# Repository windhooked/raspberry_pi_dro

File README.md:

# raspberry_pi_dro
Raspberry PI DRO for the Lathe, with Frequency drive control and soft stops

If you ever thought a manual lathe could be more intelligent, and a CNC lathe takes too long to program for one of jobs, this project might be for you. Thread cutting, the cut cycle is slow, the backout cycle is just as painfully slow. It wwoul dbe nice to have a seperate speed for cut and backout cycles.

Features:

1) Simple button controls for forward / Reverse and Stop
2) Set speed on forward and reverse cycles.
3) Soft stops
4) automatic tapping function with depth and reverse out
5) Direct Glass scale interface

Controls:

[ Forward ]        [ Clear ]
[ Reverse ] [Stop] [ Enter ] [ Rotary Enc ]

Functions:
  Fwd <Ent>       " Run forward
  Fwd <Rot> < Ent> " forward with speed adjust
  Rev <Ent>        " Reverse
  Rev <Rot> <Ent>  " Reverse with speed adjust
  Stop             " Stop with break
  
  Stop <Ent>     " Set stop position based  on current Z encoder position, only active when spindle not running
  Stop <Rot> <Ent> " Set stop position with encoder based on current position, only active when spindle is not running
  
  Emergency Stop  " Stop 

Hardware:
The GPIO speed tests I have seen seem fast enough, the problem is if the cpu is busy some steps might get lost. I ahve been wanting to make use of a few HCTL2000 IC's in the parts bin. 

GPIO 3.3V to 5V
          5,6,13,16,19,20,21,26 <- D0-D7
          4  -> CLK 1-4
          23  -> SEL 1 - 4
          24  -> EN 1
          
https://github.com/machinekoder/machinekit-vagrant          
          
abyz.co.uk/rpi/pigpio/code/minimal_clk.zip

https://www.circuitsathome.com/mcu/reading-rotary-encoder-on-arduino
https://www.tansi.org/rp/interfacing5v.html
https://github.com/machinekit
https://github.com/hzeller/rpi-gpio-dma-demo
https://gist.github.com/ast/a19813fce9d34c7240091db11b8190dd

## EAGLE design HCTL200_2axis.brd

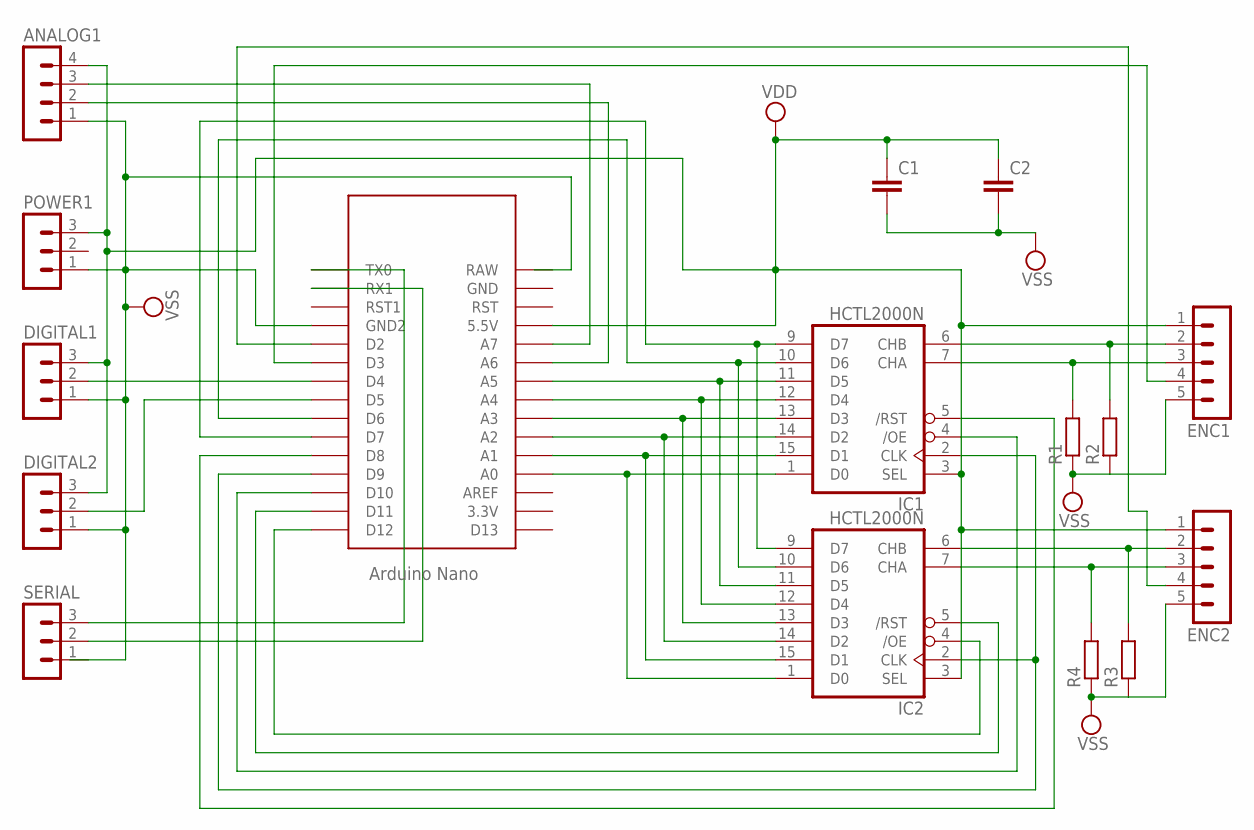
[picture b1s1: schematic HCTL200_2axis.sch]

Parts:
ANALOG1: MA04-1
C1, C2: C-EU025-030X050; C025-030X050
DIGITAL1, DIGITAL2: MA03-1
ENC1, ENC2: MA05-1
IC1, IC2: HCTL2000N; DIL16
POWER1: MA03-1
R1, R2, R3, R4: R-EU_0204/7; 0204/7
SERIAL: MA03-1
U$1: NANO

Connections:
unnamed: IC1.2 (CLK), IC2.2 (CLK), U$1.D9
unnamed: IC1.5 (/RST), U$1.D8
unnamed: IC1.1 (D0), IC2.1 (D0), U$1.A0
unnamed: IC1.15 (D1), IC2.15 (D1), U$1.A1
unnamed: IC1.14 (D2), IC2.14 (D2), U$1.A2
unnamed: IC1.13 (D3), IC2.13 (D3), U$1.A3
unnamed: IC1.12 (D4), IC2.12 (D4), U$1.A4
unnamed: IC1.11 (D5), IC2.11 (D5), U$1.A5
unnamed: IC1.10 (D6), IC2.10 (D6), U$1.D6
unnamed: IC1.9 (D7), IC2.9 (D7), U$1.D7
unnamed: ENC1.4, U$1.D3
unnamed: ENC1.2, IC1.6 (CHB), R2.2
unnamed: ENC1.3, IC1.7 (CHA), R1.2
unnamed: ENC2.2, IC2.6 (CHB), R3.2
unnamed: ENC2.3, IC2.7 (CHA), R4.2
unnamed: IC2.5 (/RST), U$1.D11
unnamed: IC1.4 (/OE), U$1.D10
unnamed: IC2.4 (/OE), U$1.D12
unnamed: ENC2.4, U$1.D2
unnamed: DIGITAL1.2, U$1.D4
unnamed: DIGITAL2.2, U$1.D5
unnamed: ANALOG1.2, U$1.A6
unnamed: ANALOG1.3, U$1.A7
unnamed: SERIAL.2, U$1.RX1
unnamed: SERIAL.3, U$1.TX0
VDD: ANALOG1.4, C1.1, C2.1, DIGITAL1.3, DIGITAL2.3, ENC1.1, ENC2.1, IC1.3 (SEL), IC1.16 (VDD), IC2.3 (SEL), IC2.16 (VDD), POWER1.3, U$1.5V (5.5V)
VSS: ANALOG1.1, C1.2, C2.2, DIGITAL1.1, DIGITAL2.1, ENC1.5, ENC2.5, IC1.8 (VSS), IC2.8 (VSS), POWER1.1, R1.1, R2.1, R3.1, R4.1, U$1.GND1 (GND2)

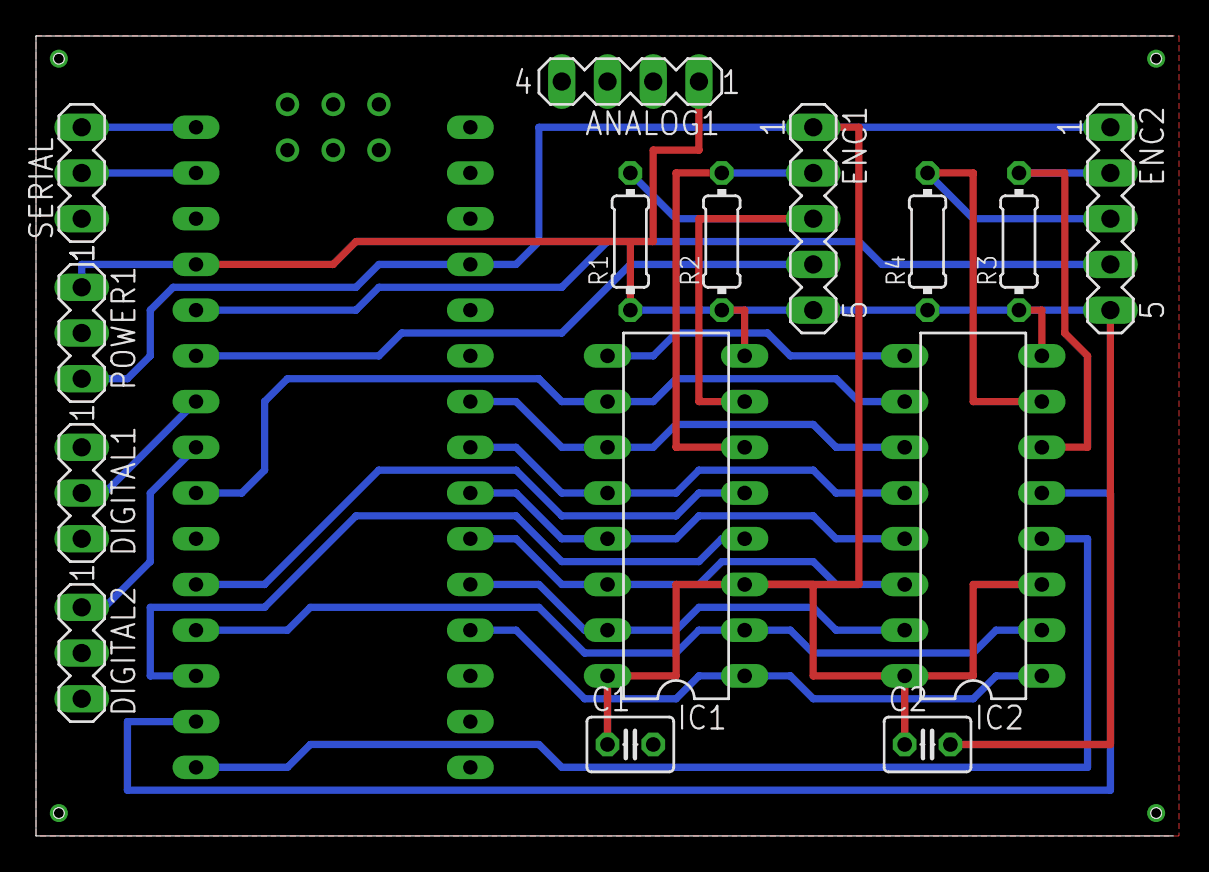
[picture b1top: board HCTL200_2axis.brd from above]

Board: 2 copper layers, 63.2 x 44.4 mm, 18 parts (0 on the bottom side), 27 nets.

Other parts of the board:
U$2, U$3: 3,0

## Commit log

2018-08-25 Update arduino_hctl2000.ino
    First test on breadboard with some pin changes and clock generation with Arduino.
2018-08-25 Update arduino_hctl2000.ino
    Update push button scan logic
